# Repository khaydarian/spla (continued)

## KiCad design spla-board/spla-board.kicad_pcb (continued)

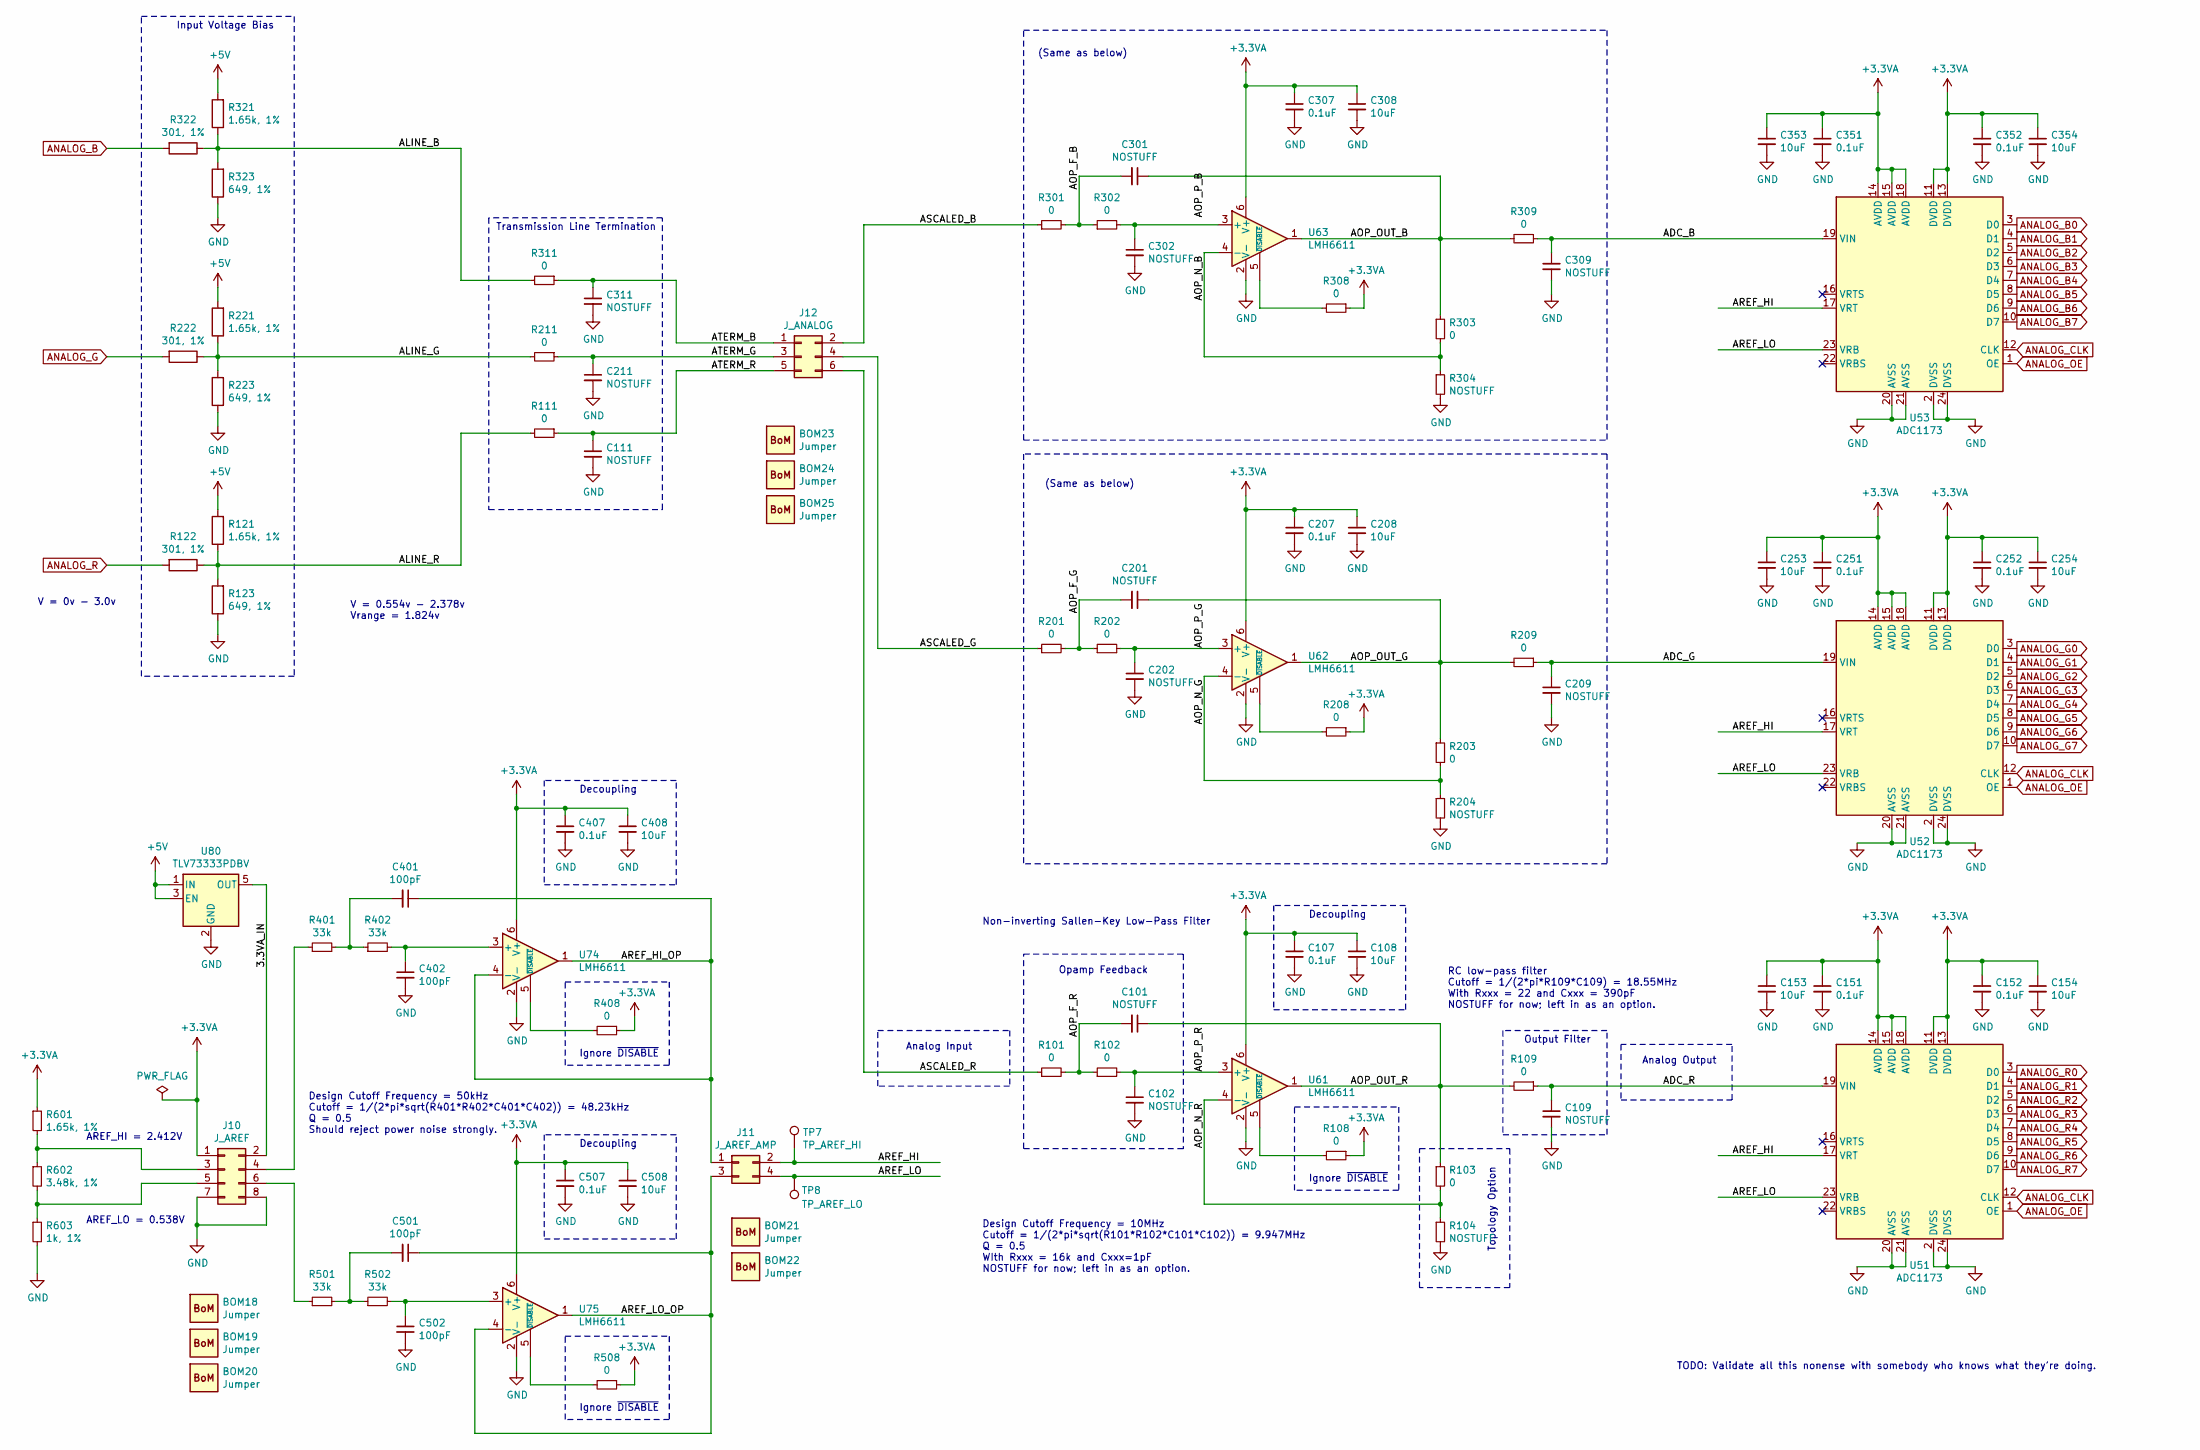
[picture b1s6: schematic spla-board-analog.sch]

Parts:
BOM18, BOM19, BOM20, BOM21, BOM22, BOM23, BOM24, BOM25: Jumper; BoM; Digikey S9337-ND
C101, C102, C109, C111, C201, C202, C209, C211, C301, C302, C309, C311: NOSTUFF; C_0603_1608Metric; Digikey N/A
C107, C151, C152, C207, C251, C252, C307, C351, C352, C407, C507: 0.1uF; C_0603_1608Metric; Digikey 490-16477-1-ND
C108, C153, C154, C208, C253, C254, C308, C353, C354, C408, C508: 10uF; C_0603_1608Metric; Digikey 490-12538-1-ND
C401, C402, C501, C502: 100pF; C_0603_1608Metric; Digikey 490-4771-1-ND
J10: J_AREF; PinHeader_2x04_P2.54mm_Vertical; Digikey S2011EC-40-ND
J11: J_AREF_AMP; PinHeader_2x02_P2.54mm_Vertical; Digikey S2011EC-40-ND
J12: J_ANALOG; PinHeader_2x03_P2.54mm_Vertical; Digikey S2011EC-40-ND
R101, R102, R103, R108, R109, R111, R201, R202, R203, R208, R209, R211, R301, R302, R303, R308, R309, R311, R408, R508: 0; R_0603_1608Metric; Digikey 2019-RK73Z1JTTDCT-ND
R104, R204, R304: NOSTUFF; R_0603_1608Metric; Digikey N/A
R121, R221, R321, R601: 1.65k, 1%; R_0603_1608Metric; Digikey RMCF0603FT1K65CT-ND
R122, R222, R322: 301, 1%; R_0603_1608Metric; Digikey RMCF0603FT301RCT-ND
R123, R223, R323: 649, 1%; R_0603_1608Metric; Digikey RMCF0603FT649RCT-ND
R401, R402, R501, R502: 33k; R_0603_1608Metric; Digikey RMCF0603JT33K0CT-ND
R602: 3.48k, 1%; R_0603_1608Metric; Digikey RMCF0603FT3K48CT-ND
R603: 1k, 1%; R_0603_1608Metric; Digikey RMCF0603FT1K00CT-ND
TP7: TP_AREF_HI; TestPoint_Pad_D1.0mm; Digikey N/A
TP8: TP_AREF_LO; TestPoint_Pad_D1.0mm; Digikey N/A
U51, U52, U53: ADC1173; TSSOP-24_4.4x7.8mm_P0.65mm; Digikey 296-35234-1-ND
U61, U62, U63, U74, U75: LMH6611; TSOT-23-6; Digikey 296-41441-1-ND
U80: TLV73333PDBV; SOT-23-5; Digikey 296-40673-1-ND

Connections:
+3.3VA: C107.1, C108.1, C151.1, C152.1, C153.1, C154.1, C207.1, C208.1, C251.1, C252.1, C253.1, C254.1, C307.1, C308.1, C351.1, C352.1, C353.1, C354.1, C407.1, C408.1, C507.1, C508.1, J10.1, R108.1, R208.1, R308.1, R408.1, R508.1, R601.1, U51.11 (DVDD), U51.13 (DVDD), U51.14 (AVDD), U51.15 (AVDD), U51.18 (AVDD), U52.11 (DVDD), U52.13 (DVDD), U52.14 (AVDD), U52.15 (AVDD), U52.18 (AVDD), U53.11 (DVDD), U53.13 (DVDD), U53.14 (AVDD), U53.15 (AVDD), U53.18 (AVDD), U61.6 (V+), U62.6 (V+), U63.6 (V+), U74.6 (V+), U75.6 (V+)
+5V: R121.2, R221.2, R321.2, U80.1 (IN), U80.3 (EN); also elsewhere on the board
/SPLA Board - Analog/3.3VA_IN: J10.2, U80.5 (OUT)
/SPLA Board - Analog/ADC_B: C309.1, R309.1, U53.19 (VIN)
/SPLA Board - Analog/ADC_G: C209.1, R209.1, U52.19 (VIN)
/SPLA Board - Analog/ADC_R: C109.1, R109.1, U51.19 (VIN)
/SPLA Board - Analog/ALINE_B: R311.2, R321.1, R322.1, R323.2
/SPLA Board - Analog/ALINE_G: R211.2, R221.1, R222.1, R223.2
/SPLA Board - Analog/ALINE_R: R111.2, R121.1, R122.1, R123.2
/SPLA Board - Analog/AOP_F_B: C301.2, R301.2, R302.1
/SPLA Board - Analog/AOP_F_G: C201.2, R201.2, R202.1
/SPLA Board - Analog/AOP_F_R: C101.2, R101.2, R102.1
/SPLA Board - Analog/AOP_N_B: R303.2, R304.1, U63.4 (-)
/SPLA Board - Analog/AOP_N_G: R203.2, R204.1, U62.4 (-)
/SPLA Board - Analog/AOP_N_R: R103.2, R104.1, U61.4 (-)
/SPLA Board - Analog/AOP_OUT_B: C301.1, R303.1, R309.2, U63.1
/SPLA Board - Analog/AOP_OUT_G: C201.1, R203.1, R209.2, U62.1
/SPLA Board - Analog/AOP_OUT_R: C101.1, R103.1, R109.2, U61.1
/SPLA Board - Analog/AOP_P_G: C202.1, R202.2, U62.3 (+)
/SPLA Board - Analog/AOP_P_R: C102.1, R102.2, U61.3 (+)
/SPLA Board - Analog/AREF_HI: J11.2, TP7.1, U51.17 (VRT), U52.17 (VRT), U53.17 (VRT)
/SPLA Board - Analog/AREF_HI_OP: C401.1, J11.1, U74.1, U74.4 (-)
/SPLA Board - Analog/AREF_LO: J11.4, TP8.1, U51.23 (VRB), U52.23 (VRB), U53.23 (VRB)
/SPLA Board - Analog/AREF_LO_OP: C501.1, J11.3, U75.1, U75.4 (-)
/SPLA Board - Analog/ASCALED_B: J12.2, R301.1
/SPLA Board - Analog/ASCALED_G: J12.4, R201.1
/SPLA Board - Analog/ASCALED_R: J12.6, R101.1
/SPLA Board - Analog/ATERM_B: C311.1, J12.1, R311.1
/SPLA Board - Analog/ATERM_G: C211.1, J12.3, R211.1
/SPLA Board - Analog/ATERM_R: C111.1, J12.5, R111.1
ANALOG_B: R322.2; also elsewhere on the board
ANALOG_B0: U53.3 (D0); also elsewhere on the board
ANALOG_B1: U53.4 (D1); also elsewhere on the board
ANALOG_B2: U53.5 (D2); also elsewhere on the board
ANALOG_B3: U53.6 (D3); also elsewhere on the board
ANALOG_B4: U53.7 (D4); also elsewhere on the board
ANALOG_B5: U53.8 (D5); also elsewhere on the board
ANALOG_B6: U53.9 (D6); also elsewhere on the board
ANALOG_B7: U53.10 (D7); also elsewhere on the board
ANALOG_CLK: U51.12 (CLK), U52.12 (CLK), U53.12 (CLK); also elsewhere on the board
ANALOG_G: R222.2; also elsewhere on the board
ANALOG_G0: U52.3 (D0); also elsewhere on the board
ANALOG_G1: U52.4 (D1); also elsewhere on the board
ANALOG_G2: U52.5 (D2); also elsewhere on the board
ANALOG_G3: U52.6 (D3); also elsewhere on the board
ANALOG_G4: U52.7 (D4); also elsewhere on the board
ANALOG_G5: U52.8 (D5); also elsewhere on the board
ANALOG_G6: U52.9 (D6); also elsewhere on the board
ANALOG_G7: U52.10 (D7); also elsewhere on the board
ANALOG_OE: U51.1 (OE), U52.1 (OE), U53.1 (OE); also elsewhere on the board
ANALOG_R: R122.2; also elsewhere on the board
ANALOG_R0: U51.3 (D0); also elsewhere on the board
ANALOG_R1: U51.4 (D1); also elsewhere on the board
ANALOG_R2: U51.5 (D2); also elsewhere on the board
ANALOG_R3: U51.6 (D3); also elsewhere on the board
ANALOG_R4: U51.7 (D4); also elsewhere on the board
ANALOG_R5: U51.8 (D5); also elsewhere on the board
ANALOG_R6: U51.9 (D6); also elsewhere on the board
ANALOG_R7: U51.10 (D7); also elsewhere on the board
GND: C102.2, C107.2, C108.2, C109.2, C111.2, C151.2, C152.2, C153.2, C154.2, C202.2, C207.2, C208.2, C209.2, C211.2, C251.2, C252.2, C253.2, C254.2, C302.2, C307.2, C308.2, C309.2, C311.2, C351.2, C352.2, C353.2, C354.2, C402.2, C407.2, C408.2, C502.2, C507.2, C508.2, J10.7, J10.8, R104.2, R123.1, R204.2, R223.1, R304.2, R323.1, R603.2, U51.2 (DVSS), U51.20 (AVSS), U51.21 (AVSS), U51.24 (DVSS), U52.2 (DVSS), U52.20 (AVSS), U52.21 (AVSS), U52.24 (DVSS), U53.2 (DVSS), U53.20 (AVSS), U53.21 (AVSS), U53.24 (DVSS), U61.2 (V-), U62.2 (V-), U63.2 (V-), U74.2 (V-), U75.2 (V-), U80.2 (GND); also elsewhere on the board
unnamed: C302.1, R302.2, U63.3 (+)
unnamed: C401.2, R401.2, R402.1
unnamed: C402.1, R402.2, U74.3 (+)
unnamed: C501.2, R501.2, R502.1
unnamed: C502.1, R502.2, U75.3 (+)
unnamed: J10.3, R601.2, R602.1
unnamed: J10.4, R401.1
unnamed: J10.5, R602.2, R603.1
unnamed: J10.6, R501.1
unnamed: R108.2, U61.5 (~DISABLE)
unnamed: R208.2, U62.5 (~DISABLE)
unnamed: R308.2, U63.5 (~DISABLE)
unnamed: R408.2, U74.5 (~DISABLE)
unnamed: R508.2, U75.5 (~DISABLE)

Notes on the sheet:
AREF_HI = 2.412V
AREF_LO = 0.538V
V = 0v - 3.0v
TODO: Validate all this nonense with somebody who knows what they're doing.
Output Filter
Decoupling
Analog Input
Transmission Line Termination
Ignore ~DISABLE~
Topology Option
Opamp Feedback
Analog Output
Design Cutoff Frequency = 10MHz Cutoff = 1/(2*pi*sqrt(R101*R102*C101*C102)) = 9.947MHz Q = 0.5 WIth Rxxx = 16k and Cxxx=1pF NOSTUFF for now; left in as an option.
RC low-pass filter Cutoff = 1/(2*pi*R109*C109) = 18.55MHz With Rxxx = 22 and Cxxx = 390pF NOSTUFF for now; left in as an option.
Non-inverting Sallen-Key Low-Pass Filter
(Same as below)
V = 0.554v - 2.378v Vrange = 1.824v
Input Voltage Bias
Design Cutoff Frequency = 50kHz Cutoff = 1/(2*pi*sqrt(R401*R402*C401*C402)) = 48.23kHz Q = 0.5 Should reject power noise strongly.

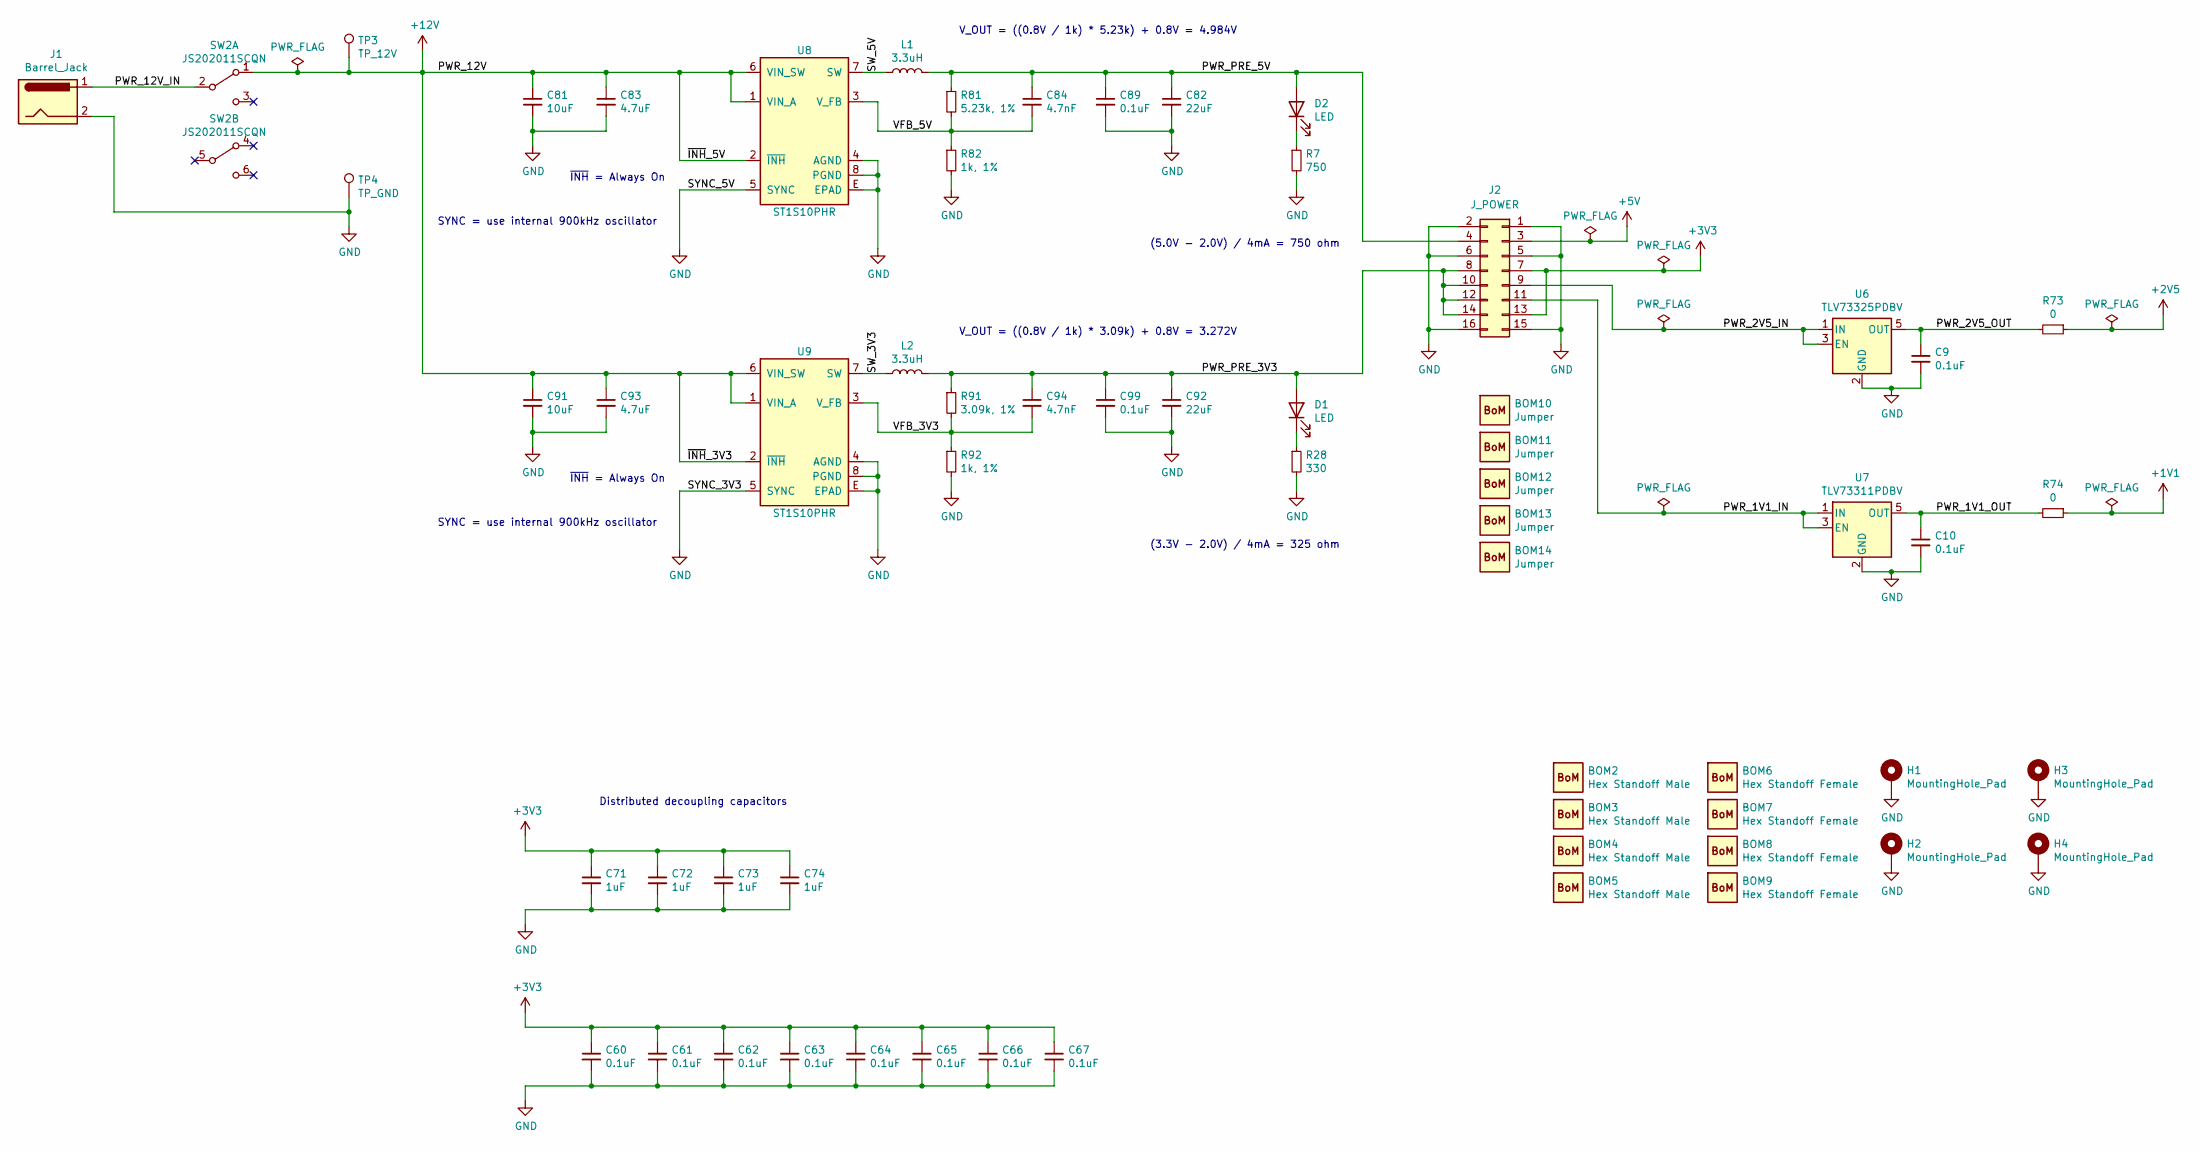
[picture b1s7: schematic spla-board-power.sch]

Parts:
BOM2, BOM3, BOM4, BOM5: Hex Standoff Male; BoM; Digikey 732-12817-ND
BOM6, BOM7, BOM8, BOM9: Hex Standoff Female; BoM; Digikey 732-12802-ND
BOM10, BOM11, BOM12, BOM13, BOM14: Jumper; BoM; Digikey S9337-ND
C9, C10, C60, C61, C62, C63, C64, C65, C66, C67, C89, C99: 0.1uF; C_0603_1608Metric; Digikey 490-16477-1-ND
C71, C72, C73, C74: 1uF; C_0603_1608Metric; Digikey 490-12699-1-ND
C81, C91: 10uF; C_0805_2012Metric; Digikey 490-10516-1-ND
C82, C92: 22uF; C_0805_2012Metric; Digikey 490-10511-1-ND
C83, C93: 4.7uF; C_0603_1608Metric; Digikey 490-7203-1-ND
C84, C94: 4.7nF; C_0805_2012Metric; Digikey 490-8289-1-ND
D1, D2: LED; LED_0805_2012Metric; Digikey 732-4986-1-ND
H1, H2, H3, H4: MountingHole_Pad; MountingHole_3.2mm_M3_Pad; Digikey N/A
J1: Barrel_Jack; BarrelJack_CUI_PJ-036AH-SMT_Horizontal; Digikey CP-036AHPJCT-ND
J2: J_POWER; PinHeader_2x08_P2.54mm_Vertical; Digikey S2011EC-40-ND
L1, L2: 3.3uH; L_Vishay_IHLP-2020; Digikey 541-1237-1-ND
R7: 750; R_0603_1608Metric; Digikey RMCF0603JT750RCT-ND
R28: 330; R_0603_1608Metric; Digikey RMCF0603JT330RCT-ND
R73, R74: 0; R_0603_1608Metric; Digikey 2019-RK73Z1JTTDCT-ND
R81: 5.23k, 1%; R_0603_1608Metric; Digikey RMCF0603FT5K23CT-ND
R82, R92: 1k, 1%; R_0603_1608Metric; Digikey RMCF0603FT1K00CT-ND
R91: 3.09k, 1%; R_0603_1608Metric; Digikey RMCF0603FT3K09CT-ND
SW2: JS202011SCQN; Digikey 401-2002-1-ND
TP3: TP_12V; TestPoint_Pad_D2.0mm; Digikey N/A
TP4: TP_GND; TestPoint_Pad_D2.0mm; Digikey N/A
U6: TLV73325PDBV; SOT-23-5; Digikey 296-40671-1-ND
U7: TLV73311PDBV; SOT-23-5; Digikey 296-40663-1-ND
U8, U9: ST1S10PHR; ST_PowerSO-8EP_4x5mm_P1.27mm_EP3.5x2.6mm; Digikey 497-6904-1-ND

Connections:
+1V1: R74.1; also elsewhere on the board
+2V5: R73.1; also elsewhere on the board
+5V: J2.3; also elsewhere on the board
+12V: C81.1, C83.1, C91.1, C93.1, SW2.1 (A), TP3.1, U8.1 (VIN_A), U8.2 (~INH), U8.6 (VIN_SW), U9.1 (VIN_A), U9.2 (~INH), U9.6 (VIN_SW)
/SPLA Board - Power/PWR_1V1_IN: J2.11, U7.1 (IN), U7.3 (EN)
/SPLA Board - Power/PWR_1V1_OUT: C10.1, R74.2, U7.5 (OUT)
/SPLA Board - Power/PWR_2V5_IN: J2.9, U6.1 (IN), U6.3 (EN)
/SPLA Board - Power/PWR_2V5_OUT: C9.1, R73.2, U6.5 (OUT)
/SPLA Board - Power/PWR_12V_IN: J1.1, SW2.2 (B)
/SPLA Board - Power/PWR_PRE_3V3: C92.1, C94.1, C99.1, D1.2 (A), J2.8, J2.10, J2.12, J2.14, L2.2, R91.1
/SPLA Board - Power/PWR_PRE_5V: C82.1, C84.1, C89.1, D2.2 (A), J2.4, L1.2, R81.1
/SPLA Board - Power/SW_3V3: L2.1, U9.7 (SW)
/SPLA Board - Power/SW_5V: L1.1, U8.7 (SW)
/SPLA Board - Power/VFB_3V3: C94.2, R91.2, R92.1, U9.3 (V_FB)
/SPLA Board - Power/VFB_5V: C84.2, R81.2, R82.1, U8.3 (V_FB)
GND: C9.2, C10.2, C60.2, C61.2, C62.2, C63.2, C64.2, C65.2, C66.2, C67.2, C71.2, C72.2, C73.2, C74.2, C81.2, C82.2, C83.2, C89.2, C91.2, C92.2, C93.2, C99.2, H1.1, H2.1, H3.1, H4.1, J1.2, J2.1, J2.2, J2.5, J2.6, J2.15, J2.16, R7.2, R28.2, R82.2, R92.2, TP4.1, U6.2 (GND), U7.2 (GND), U8.4 (AGND), U8.5 (SYNC), U8.8 (PGND), U8.E (EPAD), U9.4 (AGND), U9.5 (SYNC), U9.8 (PGND), U9.E (EPAD); also elsewhere on the board
unnamed: D1.1 (K), R28.1
unnamed: D2.1 (K), R7.1

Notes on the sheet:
SYNC = use internal 900kHz oscillator
V_OUT = ((0.8V / 1k) * 5.23k) + 0.8V = 4.984V
~INH~ = Always On
V_OUT = ((0.8V / 1k) * 3.09k) + 0.8V = 3.272V
(5.0V - 2.0V) / 4mA = 750 ohm
(3.3V - 2.0V) / 4mA = 325 ohm
Distributed decoupling capacitors

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
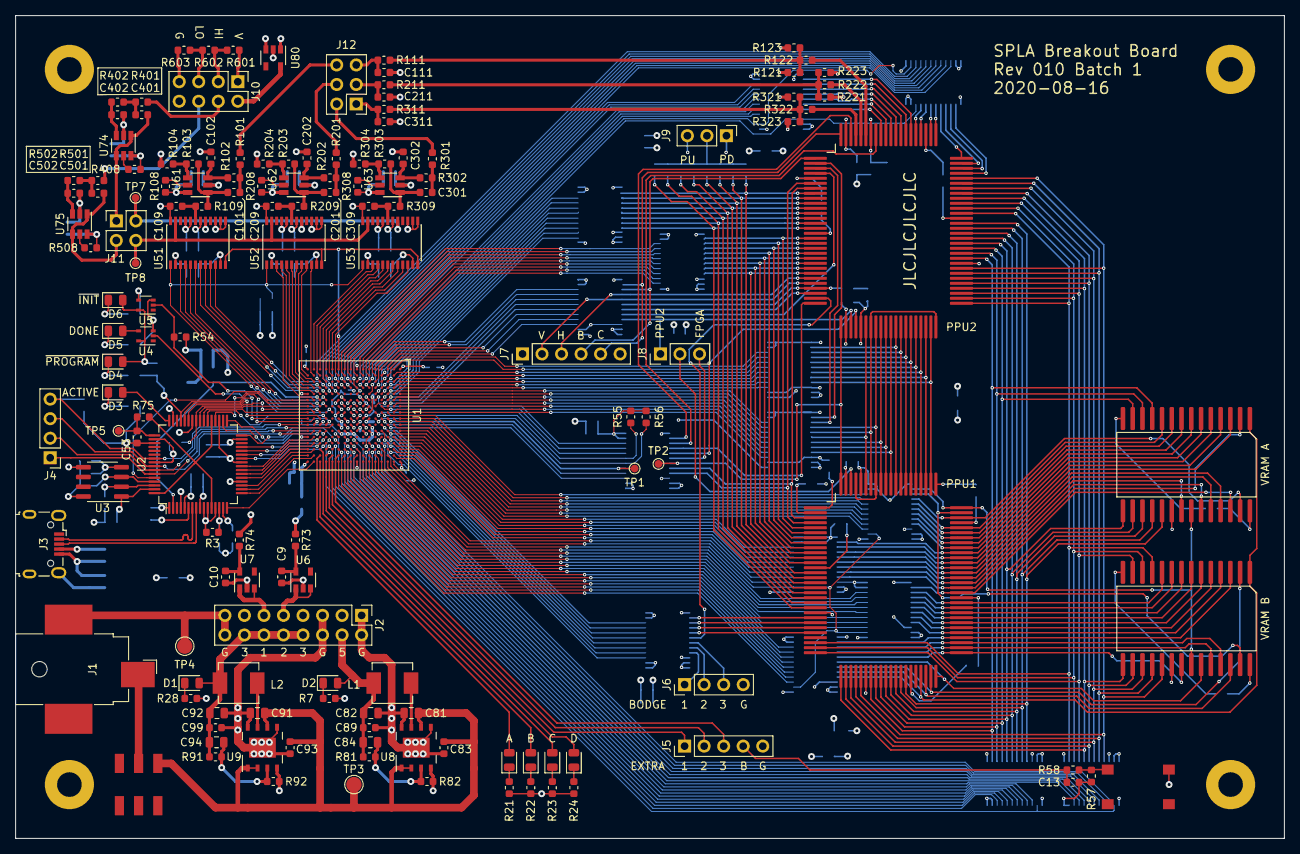
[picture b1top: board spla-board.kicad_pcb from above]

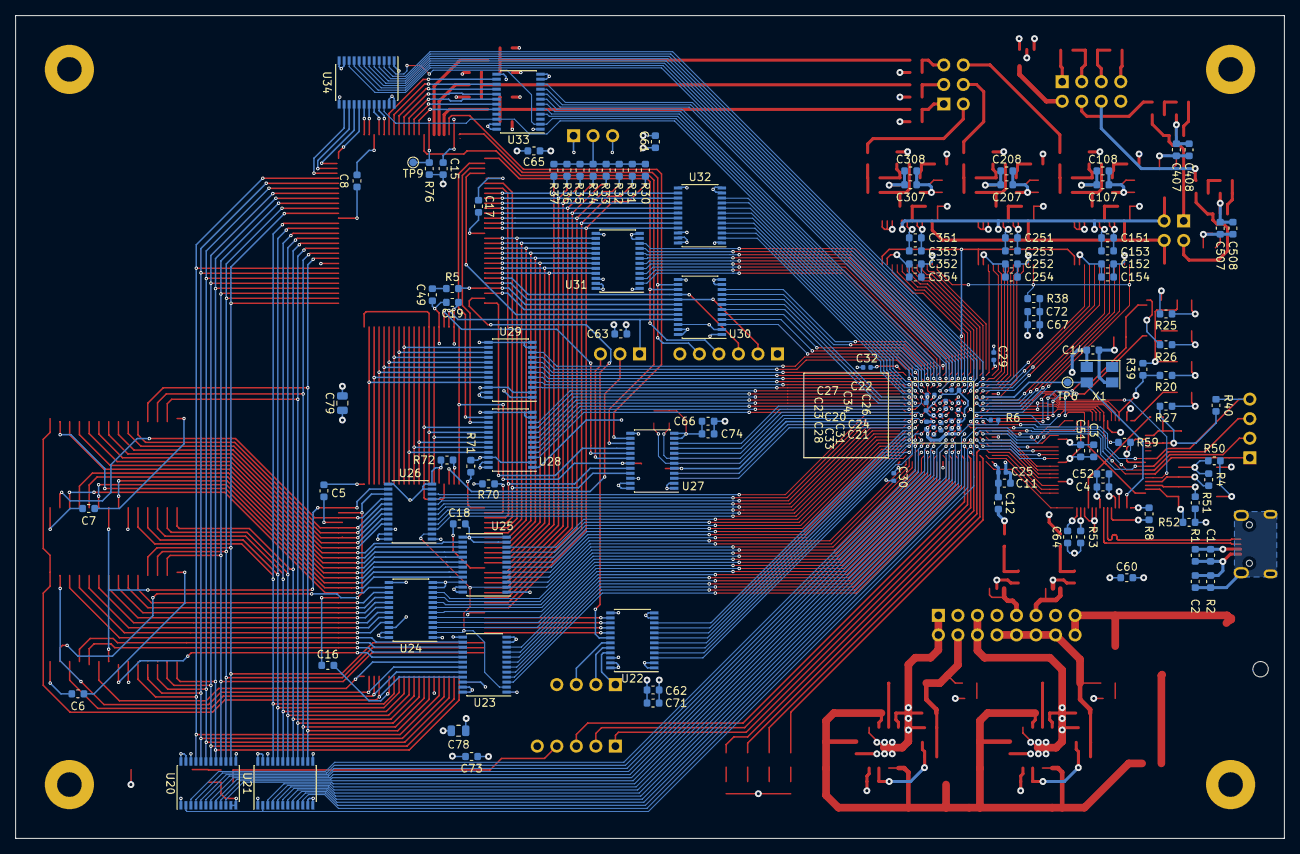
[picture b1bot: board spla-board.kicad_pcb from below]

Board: 4 copper layers, 165.0 x 107.0 mm, 290 parts (118 on the bottom side), 404 nets.

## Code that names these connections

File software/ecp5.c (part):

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
// BCBUS (B-interface high)
#define LED3_BIT 0x01
#define JTAG_TCK 0x10
#define JTAG_TDI 0x20
#define JTAG_TDO 0x40
#define JTAG_TMS 0x80

status ecp5_init() {
  const char* frequency = "30MHz";
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
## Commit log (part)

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2020-04-17 accounting: Split inventory files.
2020-04-17 pcb: Tweak +1V1 decoupling capacitors.
2020-04-18 inventory: Received chips.
2020-04-18 software: Refactor out show_ftdi_error.
2020-04-19 software: Split to multiple source files.
2020-04-20 software: Add FTDI test commands, partial MPSSE support, write buffering.
2020-04-20 blog: Overdue update. PCB, Design Review, Software MPSSE.
2020-04-22 schematic: Add Digikey and ManufacturerId fields to big components.
2020-04-23 schematic: Add part numbers for USB and power jack.
2020-04-25 schematic: Lower-case 'k' in resistors.
2020-04-25 schematic: Add part numbers for pinheaders (albeit that these are breakaways, and it's not one-per-part).
2020-04-25 schematic/pcb: Swap oscillator for FOX924 equivalent.
2020-04-25 pcb: Add trivial traceability markings.
2020-04-25 schematic/pcb: Add test points for remaining three FPGA pins.
2020-04-25 schematic/pcb: Add footprints for large input capacitors, NOSTUFF for now.
2020-04-25 schematic/pcb: Add pullup to SPI_CS and pulldown to PPU2_RESET.
2020-04-26 bom: Rearrange scripts.
2020-04-26 pm: Update README.
2020-04-27 bom: Add digikey bulk-add-format script.
2020-04-27 pcb: Shrink power/ground fill spacing to 0.2mm around FPGA.
    The KiCad default here (0.508mm) is probably larger than necessary. Also
    remove most of the redundant traces that were trying to fix the fill not
    getting through the gaps between vias. I could apply this across the entire
    board, but that seems like a bad idea for the larger vias.
    It might be possible to reduce this further, but it's not worth the risk of an
    impossible-to-fix plane-to-via short.
2020-04-27 schematic: Export revision 9.
2020-04-27 pcb: Export revision 9.
2020-05-02 accounting: Partially add hot air rework station and power bricks.
2020-05-02 todo: Drop or defer a bunch of items.
2020-05-02 accounting: Add second Digikey order.
2020-05-02 accounting: Second SNES arrived.
2020-05-02 accounting: Move packages to their own file; Update with amazon order info.
2020-05-02 software: Replace error handling with 'status' object.
2020-05-02 pm: Fix typos.
2020-05-03 accounting: Order bench power supply and solder.
2020-05-03 schematic: Rename LED[46] to LED[78], to match silkscreen.
2020-05-04 rtl: Create initial RTL build system; add bringup_blinky and dummy modules.
2020-05-06 rtl: Replace inout/Z with explicit signals and TRELLIS_IO primitives.
2020-05-07 rtl: Rename 'fifo' to 'ftdi_fifo' for clarity.
2020-05-07 pm: Update status in README.
2020-05-10 rtl: Switch to list-of-files in Makefile.
2020-05-11 software: Clean up MPSSE driver a bit.
2020-05-11 software: Add warning when exiting with un-flushed writes.
2020-05-11 software: Add mpsse_read_data and ftdiutil support.
2020-05-11 rtl: Switch to correct ECP device model (previoulsy typo'd).
2020-05-11 software: Rename 'ftdiutil' to match function prefix.
2020-05-13 accounting: First boards (r009) arrived.
2020-05-13 todo: Add section for future board revision items.
2020-05-15 blog: Update. Bringup phase 2; stuck on FTDI 1.8V rail.
2020-05-17 blog: FTDI chip now working, but USB is not.
2020-05-17 blog: Still stuck on USB.
2020-05-18 blog: Notes on software for FTDI.
2020-05-18 software: Add ftdiutil_set_interface.
2020-05-19 software: Wrap ftdi_usb_get_strings to handle empty serial field.
2020-05-20 design: Add some more mistakes.
2020-05-21 software: Add bringup_ftdi.
2020-05-22 software: Rework bringup_ftdi to show all bad states.
2020-05-22 blog: Cleared all the FTDI bridges.
2020-05-22 pm: Fix typo in README.
2020-05-22 software: Fix 'cable' open, as it doesn't have two interfaces.
2020-05-23 accounting: Update board parts inventory.
2020-05-23 doc: Move mistakes, and add a few details.
2020-05-24 accounting: Add lint script.
2020-05-25 software: Fix build glitch with ftdi_i.h
2020-05-25 todo: Add item.
2020-05-27 blog: FPGA reflow attempt #2, also failed.
2020-05-27 software: Fix pin numbers in bringup_ftdi.
2020-05-29 blog: FPGA Reflow attempt #3, which seems to have mostly worked.
2020-05-29 software: Add debug logging to ftdiutil.
2020-05-29 software: Add clang-format to build system.
2020-05-30 schematic/pcb: Update for new KiCad version; no meaningfuly changes.
2020-05-30 software: Add partial code to load FPGA bitstreams into the ECP5.
2020-05-30 software: Add assertions to mpsse_{read,write,transfer}_data.
2020-05-30 blog: ECP5 SPI Slave configuration mode.
2020-05-30 software: Tweak main to flush stdout for errors.
2020-05-30 software: Add very crude bitstream parser, and show_bitstream.
2020-05-30 software: Add fpga_test_ids, and ecp5_status.
2020-05-30 software: Change bitstream_parse callbacks to return status.
2020-05-31 software: Add load_bitstream and supporting code.
2020-05-31 blog: Still no luck with load_bitstream.
2020-05-31 software: Cleanup ECP5 constant mess.
2020-06-04 software: Push ECP5 SPI frequency up to 6MHz.
2020-06-04 software: Try setting DONE explicitly; no luck.
2020-06-05 software: More random changes trying to get the FPGA to wake up.
2020-06-14 accounting: Add sockets.
2020-06-17 software: Add a stream of idle bytes at the end of bitstream loading.
2020-06-17 software: Move idle bytes to after releasing PROGRAMN; still no good.
2020-06-17 software: Revert Driving DONE high explicitly.
2020-06-18 rtl: Rewrite bringup.v to avoid driving usb pins; sample both clocks.
2020-06-19 blog: Fix typo sentence.
2020-06-20 software: Add working standalone SSPI bitstream loader.
2020-06-20 rtl: Remove bringup_blinky image (bringup image is ok for now).
2020-06-20 rtl: Configure internal osciallator to ~12MHz.
2020-06-20 rtl: Enable bitstream compression.
2020-06-20 rtl: Add bringup_uart.
2020-06-20 software: Refactor bitstream.
2020-06-20 rtl: Fix Makefile glitch.
2020-06-20 rtl/software: Change UART speed to 115200 baud.
2020-06-21 verif: Add framework for verilator-based verification.
2020-06-23 rtl: Rename 'clk' to 'clock'.
2020-06-24 rtl: Refactor out pulse module.
2020-06-24 software: Add --hex option to ftdi_uart.
2020-06-24 software: Add first version of bringup_boundary tool.
2020-06-25 software: Add trivial persistence to bringup_boundary, in case I crash the board while probing.
2020-06-25 todo: Remove obsolete items.
2020-06-27 bom: Add manufacturing helper script.
2020-06-28 bom: Add overlooked parts to manufacturing helper script.
2020-06-28 software: Add convenience script bringup_fpga (for early blinker image).
2020-06-28 blog: Build log for second board. It has the same disconnected pin!
2020-06-28 accounting: Update inventory, after second board build.
2020-06-29 blog: FIFO_WR_N issue solved.
2020-06-29 software: Format.
2020-06-29 blog: Broke second board's FPGA. Oops.
2020-07-25 accounting: Add IR Preheating plate.
2020-07-25 software: Add explicit pass/fail to bringup_fifo.
2020-07-25 software: Add per-line note about ok patterns to bringup_fifo.
2020-07-25 blog: Board b002 is definitely toast.
2020-07-26 accounting: Update inventory after b001 assembly.
2020-07-26 blog: Install levelshifters; mostly works.
2020-07-27 rtl: Update brinup_levelshifter1 to use bringup_boundary's technique.
2020-07-27 blog: Level shifter inputs all work.
2020-07-27 blog: Almost done with levelshifter bringup.
2020-07-27 doc: Add more mistakes.
2020-07-29 rtl: Rename clock input to uart_tx.
2020-07-29 rtl: Add test_uart, with sync_fifo and uart_rx.
2020-07-30 WIP: broken uart testing.
2020-07-30 WIP: works, but only if uart_rx.tap_o is included.
2020-07-30 WIP: update gtkw
2020-08-01 WIP: still works.
2020-08-01 rtl/software/verif: Add test_uart, uart_rx, and supporting details.
2020-08-01 rtl: Add fifo to test_uart, with cork operation.
2020-08-02 rtl: Add unreset_by_uart, to avoid initial uart_rx glitch.
2020-08-02 bom: Add parts ordering assistance script.
2020-08-03 rtl: Refactor vram_control out of bringup_vram, for clarity.
2020-08-03 verif: Fix uart_rx build target.
2020-08-06 rtl/verif: Add verilator test for vram_control.
2020-08-06 rtl: Swap TRELLIS_IO for BB, which is equivalent.
2020-08-06 rtl/software: Add partial bringup_vram image.
2020-08-06 rtl/software: Rework bringup_vram to run operations one at a time.
2020-08-08 rtl: Remove bringup_vram_trivial.
2020-08-10 blog: Notes about VRAM issues.
2020-08-10 rtl: Add bringup_vram_steps.
2020-08-10 rtl: Remove bringup_vram_scan.
2020-08-10 blog/rtl: Painstakingly test VRAM pins.
2020-08-11 bom: Add header to reorder.py.
2020-08-11 blog: VRAM bringup complete.
2020-08-11 doc: Add a more-realistic bringup sequence.
2020-08-11 reference: Cleanup obsolete datasheets.
2020-08-11 rtl: Add bringup_ppu.
2020-08-12 accounting: Add digital calipers.
2020-08-12 schematic/pcb: Disconnect USB shield from ground.
2020-08-12 schematic/pcb: Remove unnecessary electrolytic capacitors.
2020-08-12 pcb: Move D7/D8 to a more visible location.
2020-08-12 schematic: Remove bogus library path.
2020-08-12 todo: Update some items for the next PCB revision.
2020-08-12 schematic/pcb: Consolidate analog output-enable nets, and add a pullup resistor.
    Note that this leaves two FPGA pins unused, which I'll need to correct later.
2020-08-13 schematic/pcb: Pinswap entire FPGA to put LEDs/TPs on south edge.
2020-08-13 accounting: Calipers arrived.
2020-08-14 etc: Update qfp-100 calculator script.
2020-08-14 pcb/schematic: Rework layout for 0.65mm PPU footprint, as well as other minor issues.
2020-08-15 schematic: Fix typo.
2020-08-15 schematic/pcb: Remove J4, which is unnecessary and meltable.
2020-08-15 pcb: Adjust silkscreen in several places.
2020-08-15 pcb: Rearrange power plane splits; tweak bulk decoupling.
2020-08-16 pcb: Compact left side of board by 13mm.
2020-08-16 pcb: Move USB connector slightly away from power jack.
2020-08-16 pcb: Remove GND via stitching, connect via J12 instead.
2020-08-16 schematic: Swap FTDI REF resistor from 5% (oops) to 1%.
2020-08-16 schematic/pcb: Remove unnecessary 0-ohm resistors; renumber all parts by value.
2020-08-16 accounting: Fix typo.
2020-08-16 todo: Add items around programming LEDs.
2020-08-16 todo: Add note about SNES hard-pulled pins.
2020-08-16 schematic/pcb: Seperate PPU2 AVCC; add more PPU decoupling.
2020-08-16 pcb: Move button closer to corner for physical stability.
2020-08-16 schematic/pcb: Label a few more nets properly.
2020-08-16 todo: Note about LVL_PA_DIR.
2020-08-16 todo: Add note about netlist-to-lpf idea.
2020-08-17 bom: Update scripts for ordering new parts.
2020-08-17 pcb: Remove large pads from F.Paste layer.
2020-08-17 schematic: Export revision 10.
2020-08-17 doc: Tweak manufacturing checklist.
2020-08-17 doc: Add printing / JLCPCB ordering details to manufacturing checklist.
2020-08-17 accounting/bom: Tweak lint scripts to show more than just "ok".
2020-08-17 blog: New boards ordered, with many changes.
2020-08-18 rtl/software: Rename led[78] to led_[ab], to prepare for new boards.
2020-08-21 accounting: Digikey order 4 arrived.
2020-08-23 todo: Discovered that FIFO_SIWU is on the wrong pin.
2020-08-23 software: Add attribute warn_unused_result, and fix related bugs.
2020-08-23 software: Add ftdiutil_set_bitmode_{uart,mpsse,bitbang}.
2020-08-23 software: Add ftdiutil_set_bitmode_syncff.
2020-08-23 software: Add ftdi_default_mode.
2020-08-27 bom: Update manufacture.py for new board.
2020-08-29 todo: Add note about adjacent pins on U20.
2020-08-30 bom: Remove duplicate components from manufacturing script.
2020-08-30 accounting: Update inventory and board status.
2020-08-30 accounting: Sockets arrived.
2020-08-30 software: Add bringup_first to flash ACTIVE LED.
2020-08-30 blog/doc: More bringup of b003; tweaks to bringup sequence.
2020-08-31 todo: Add note about net name typos (oops).
2020-08-31 blog: B003 bringup complete through level shifters.
2020-09-03 accounting: Add minor equipment bits; fix lint error.
2020-09-04 doc: Add button mistake.
2020-09-05 blog: Reservations about sockets.
2020-09-06 blog: Notes on games from which to get sample frames.
2020-09-09 rtl: Use misc_default in bringup_ppu.
2020-09-11 software: Rename vram_control.py to opcodes_from_rtl.py
2020-09-11 rtl/software: Add lowspeed image; based on bringup_vram.
2020-09-12 rtl/software: Add crude timing measurements; hilariously slow to run.
2020-09-14 rtl/verify: Add ppu_interrupt.
2020-09-22 software: Expand --measuretiming.
2020-09-24 software: Add trivial VCD dump for timing signals.
